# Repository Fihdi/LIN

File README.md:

# 4hp Line Level Input

The LIN (Line In) module converts any device with a headphone output (Groovebox, Radio, Laptop, Mp3-Player, etc) to Eurorack level. LIN features a high gain stereo VCA, the VCA can be used to create percussions, cutting up external audio signals or distorting existing Eurorack signals.

# VOL and CV knob

The **VOL** knob controls the base output level of the module. Modulating the output volume is possible by applying an external CV signal to the **CV** jack. The **CV** knob attenuates the incoming CV signal level.

# R and L outputs

The output jacks labeled **R** and **L** provide separate Eurorack level outputs for the right and left channels.

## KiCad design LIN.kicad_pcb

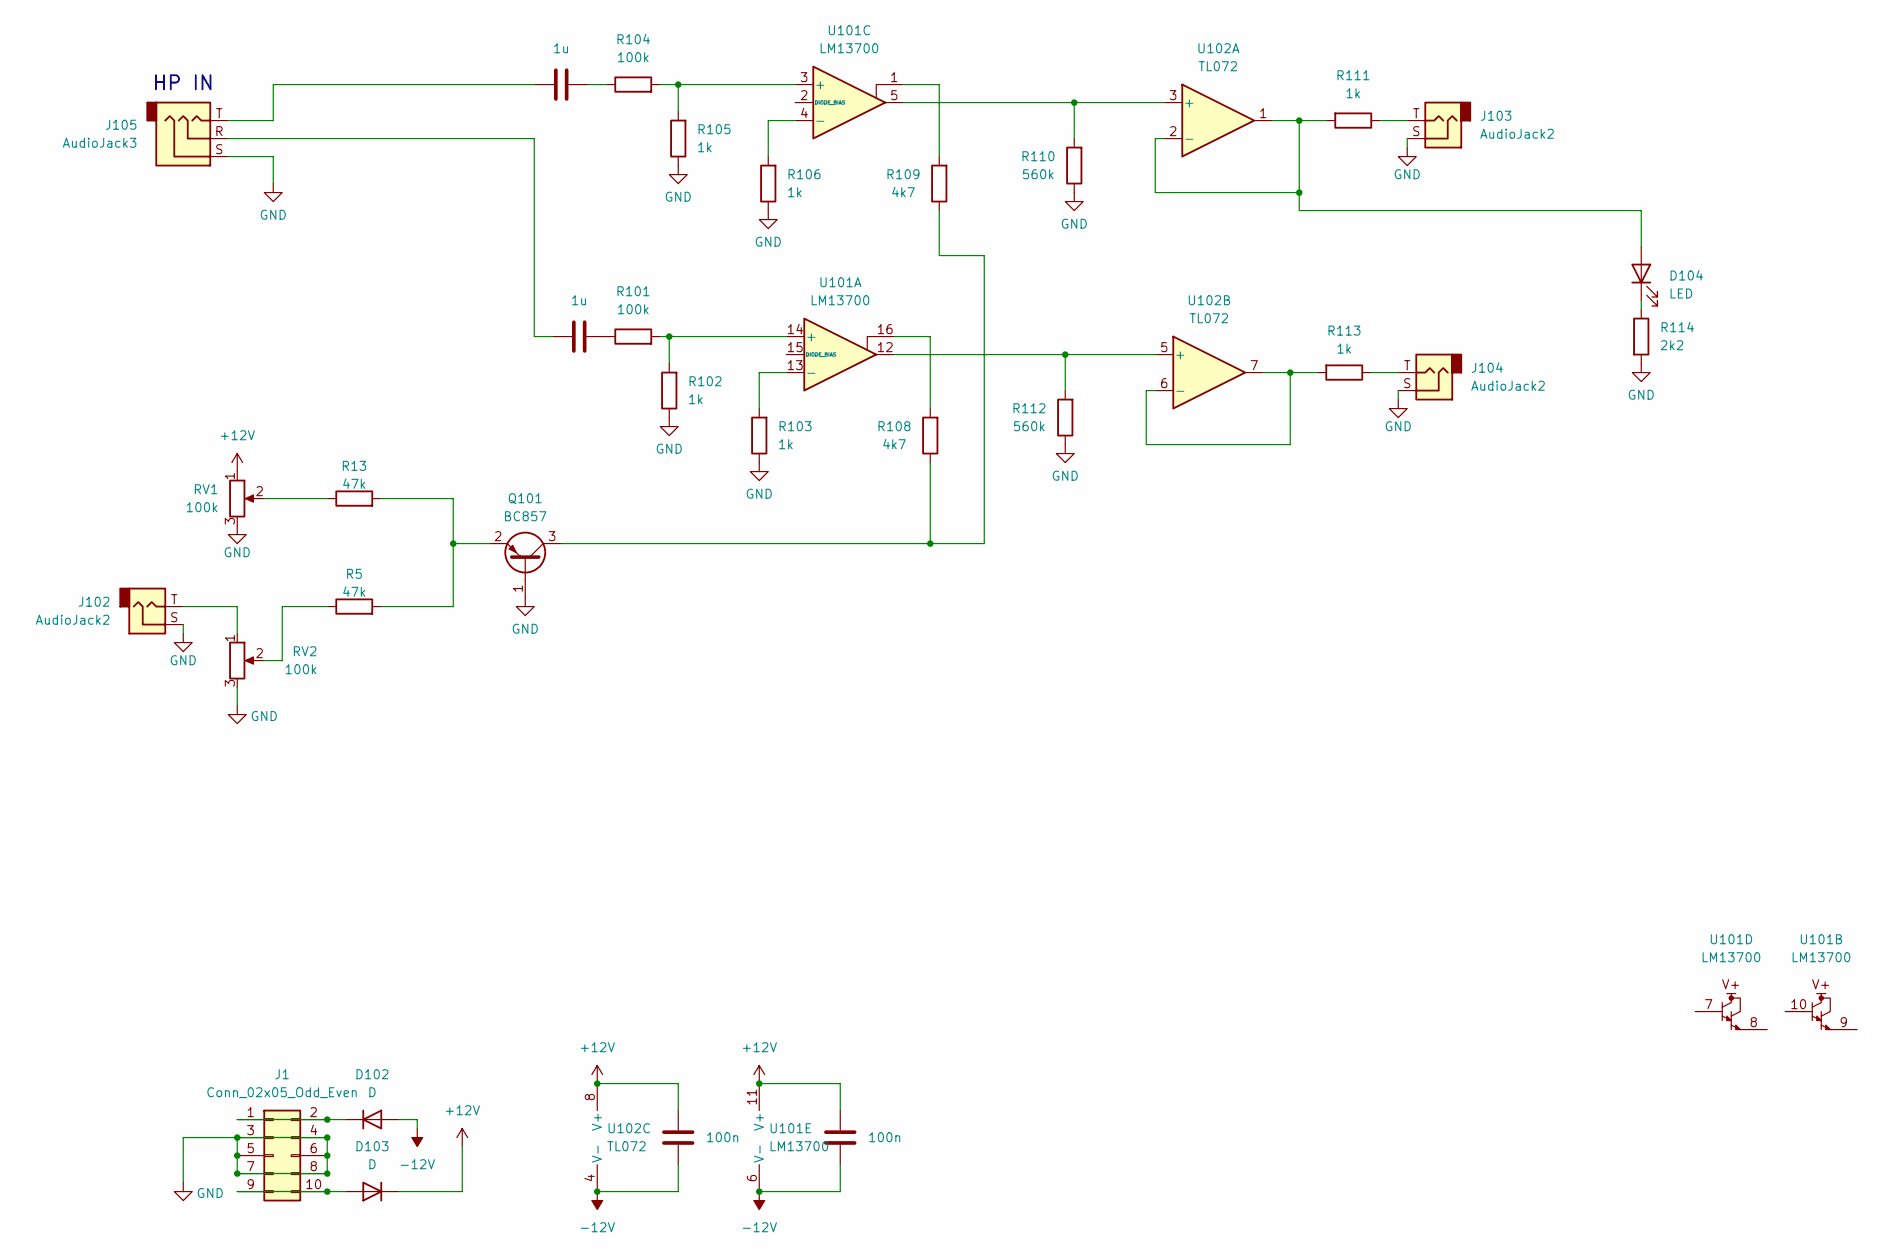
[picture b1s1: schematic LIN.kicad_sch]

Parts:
C101, C102: 1u; C_1206_3216Metric
C104, C105: 100n; C_1206_3216Metric
D102, D103: D; D_SOD-323_HandSoldering
D104: LED; LED_D5.0mm
J1: Conn_02x05_Odd_Even; IDC-Header_2x05_P2.54mm_Vertical
J102, J103, J104: AudioJack2; MonoTRS
J105: AudioJack3; StereoTRS
Q101: BC857; SOT-23
R5, R13: 47k; R_1206_3216Metric
R101, R104: 100k; R_1206_3216Metric
R102, R103, R105, R106, R111, R113: 1k; R_1206_3216Metric
R108, R109: 4k7; R_1206_3216Metric
R110, R112: 560k; R_1206_3216Metric
R114: 2k2; R_1206_3216Metric
RV1, RV2: 100k; Potentiometer_Alpha_RD901F-40-00D_Single_Vertical
U101: LM13700; SOIC-16_3.9x9.9mm_P1.27mm
U102: TL072; SOIC-8_3.9x4.9mm_P1.27mm

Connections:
+12V: C104.1, C105.1, D103.1 (K), RV1.1, U101.11 (V+), U102.8 (V+)
-12V: C104.2, C105.2, D102.2 (A), U101.6 (V-), U102.4 (V-)
GND: J1.3, J1.4, J1.5, J1.6, J1.7, J1.8, J102.S, J103.S, J104.S, J105.S, Q101.1 (B), R102.1, R103.1, R105.1, R106.1, R110.1, R112.1, R114.2, RV1.3, RV2.3
unnamed: C101.1, R101.1
unnamed: C101.2, J105.R
unnamed: C102.1, R104.1
unnamed: C102.2, J105.T
unnamed: D102.1 (K), J1.1, J1.2
unnamed: D103.2 (A), J1.9, J1.10
unnamed: D104.2 (A), R111.2, U102.1, U102.2 (-)
unnamed: D104.1 (K), R114.1
unnamed: J102.T, RV2.1
unnamed: J103.T, R111.1
unnamed: J104.T, R113.1
unnamed: Q101.3 (C), R108.1, R109.1
unnamed: Q101.2 (E), R5.2, R13.2
unnamed: R5.1, RV2.2
unnamed: R13.1, RV1.2
unnamed: R108.2, U101.16
unnamed: R109.2, U101.1
unnamed: R101.2, R102.2, U101.14 (+)
unnamed: R103.2, U101.13 (-)
unnamed: R104.2, R105.2, U101.3 (+)
unnamed: R106.2, U101.4 (-)
unnamed: R110.2, U101.5, U102.3 (+)
unnamed: R112.2, U101.12, U102.5 (+)
unnamed: R113.2, U102.6 (-), U102.7

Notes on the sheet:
HP IN

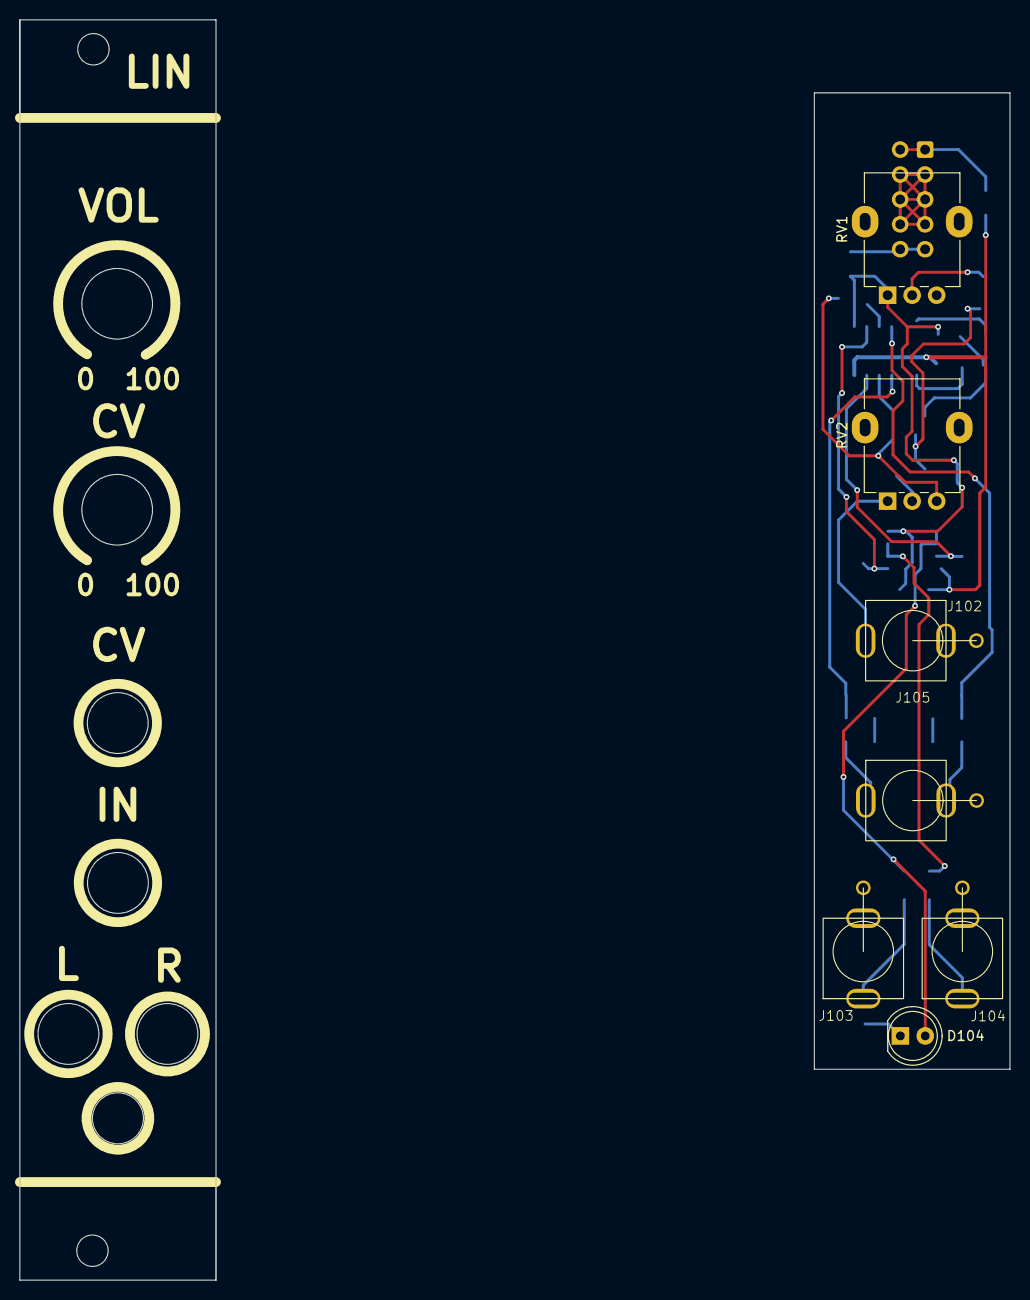
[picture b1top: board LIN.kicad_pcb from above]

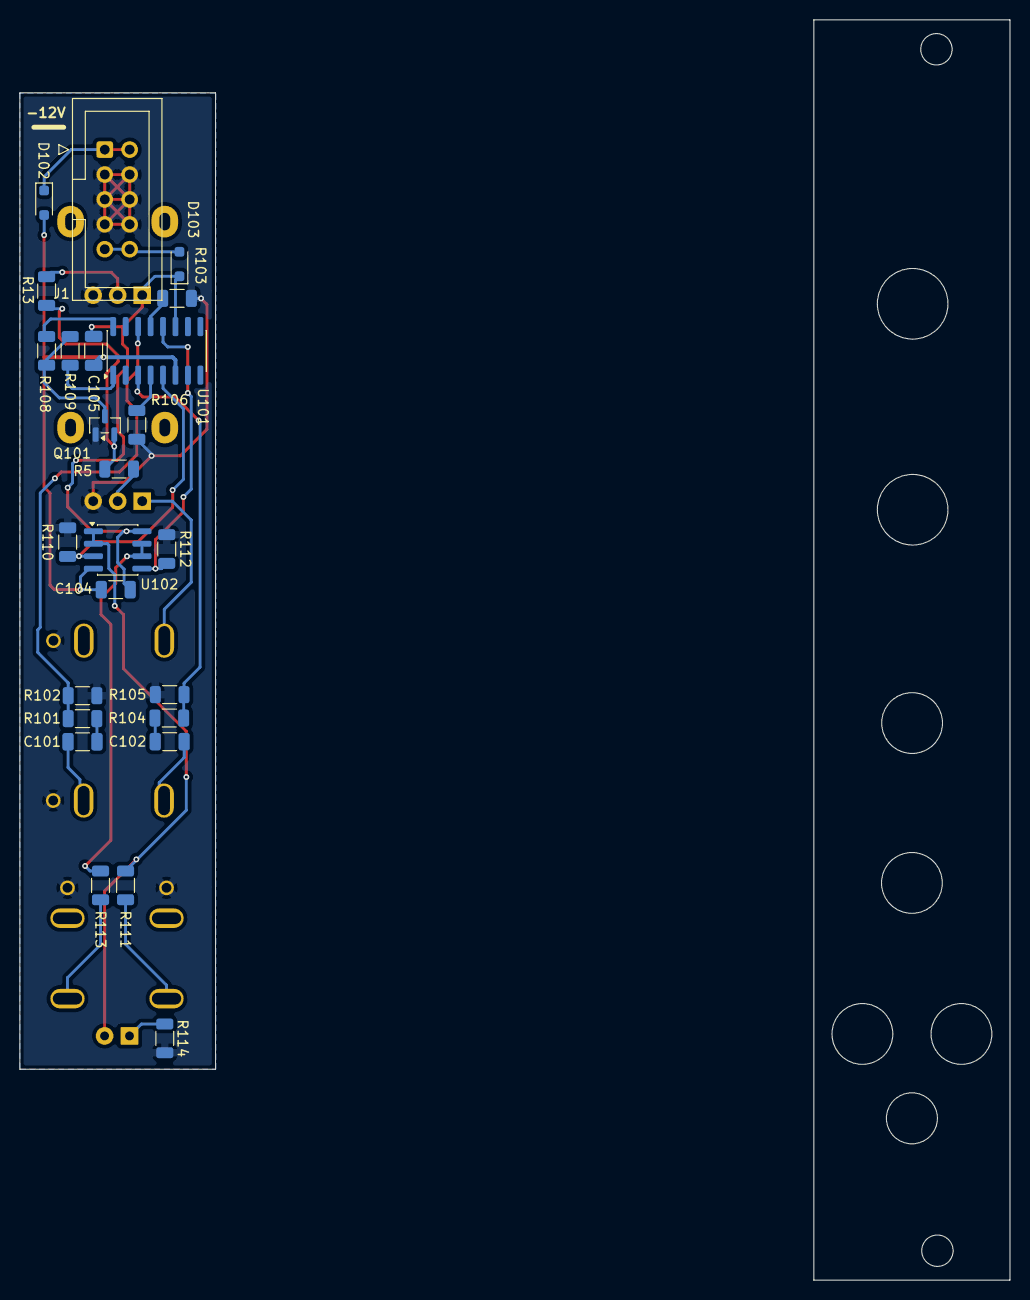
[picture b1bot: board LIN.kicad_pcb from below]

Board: 2 copper layers, 19.9 x 99.5 mm, 32 parts (25 on the bottom side), 27 nets.

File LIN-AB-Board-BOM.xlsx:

|  |  | LIN AB-Board BOM
Item # | *Designator | *Qty | Manufacturer | *Mfg Part # | Description / Value | *Package/Footprint | Type | Your Instructions / Notes
1 | C101,C102 | 2 |  | C377070 | 1u | Capacitor_SMD:C_1206_3216Metric
2 | C104,C105 | 2 |  | C309030 | 100n | Capacitor_SMD:C_1206_3216Metric
3 | D102,D103 | 2 |  | C917117 | 1N4148 | Diode_SMD:D_SOD-323_HandSoldering
4 | D104 | 1 |  |  | LED | LED_THT:LED_D5.0mm |  | DNP
5 | J1 | 1 |  |  | Conn_02x05_Odd_Even | Connector_IDC:IDC-Header_2x05_P2.54mm_Vertical |  | DNP
6 | J102,J103,J104 | 3 |  |  | AudioJack2 | Library:MonoTRS |  | DNP
7 | J105 | 1 |  |  | AudioJack3 | Library:StereoTRS |  | DNP
8 | Q101 | 1 |  | C148244 | BC857 | Package_TO_SOT_SMD:SOT-23
9 | R5,R13 | 2 |  | C2907507 | 47k | Resistor_SMD:R_1206_3216Metric
10 | R101,R104 | 2 |  | C2907421 | 100k | Resistor_SMD:R_1206_3216Metric
11 | R102,R103,R105,R106,R111,R113 | 6 |  | C131398 | 1k | Resistor_SMD:R_1206_3216Metric
12 | R108,R109 | 2 |  | C2907387 | 4k7 | Resistor_SMD:R_1206_3216Metric
13 | R110,R112 | 2 |  | C2907518 | 560k | Resistor_SMD:R_1206_3216Metric
14 | R114 | 1 |  | C2930413 | 2k2 | Resistor_SMD:R_1206_3216Metric
15 | RV1,RV2 | 2 |  |  | 100k | Potentiometer_THT:Potentiometer_Alpha_RD901F-40-00D_Single_Vertical |  | DNP
16 | U101 | 1 |  | C174050 | LM13700 | Package_SO:SOIC-16_3.9x9.9mm_P1.27mm
17 | U102 | 1 |  | C67473 | TL072 | Package_SO:SOIC-8_3.9x4.9mm_P1.27mm
Need a quick and accurante quote? Need an efficient production? Please read SMT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
Click for Instructions on How to Create a BOM
 |  |  |  |  | s
